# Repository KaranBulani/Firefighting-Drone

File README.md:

# Firefighting-Drone
This project is a drone based approach of fighting fire. It includes functionalities such as generation of area map (using sensors), generation of heat map (using sensors), detection of humans (using sensors) and measuring of toxicity levels using gas sensors. A **grant** from **Mumbai University** was received for this project.
A **research paper** for the same project has been published in **IEEE Xplore**.

To see the working of the project please checkout out the below playlist.

<div align="center">

</div>

Link to the paper **https://ieeexplore.ieee.org/document/9121043**

Link to the paper **https://eudl.eu/doi/10.4108/eai.16-5-2020.2303938**

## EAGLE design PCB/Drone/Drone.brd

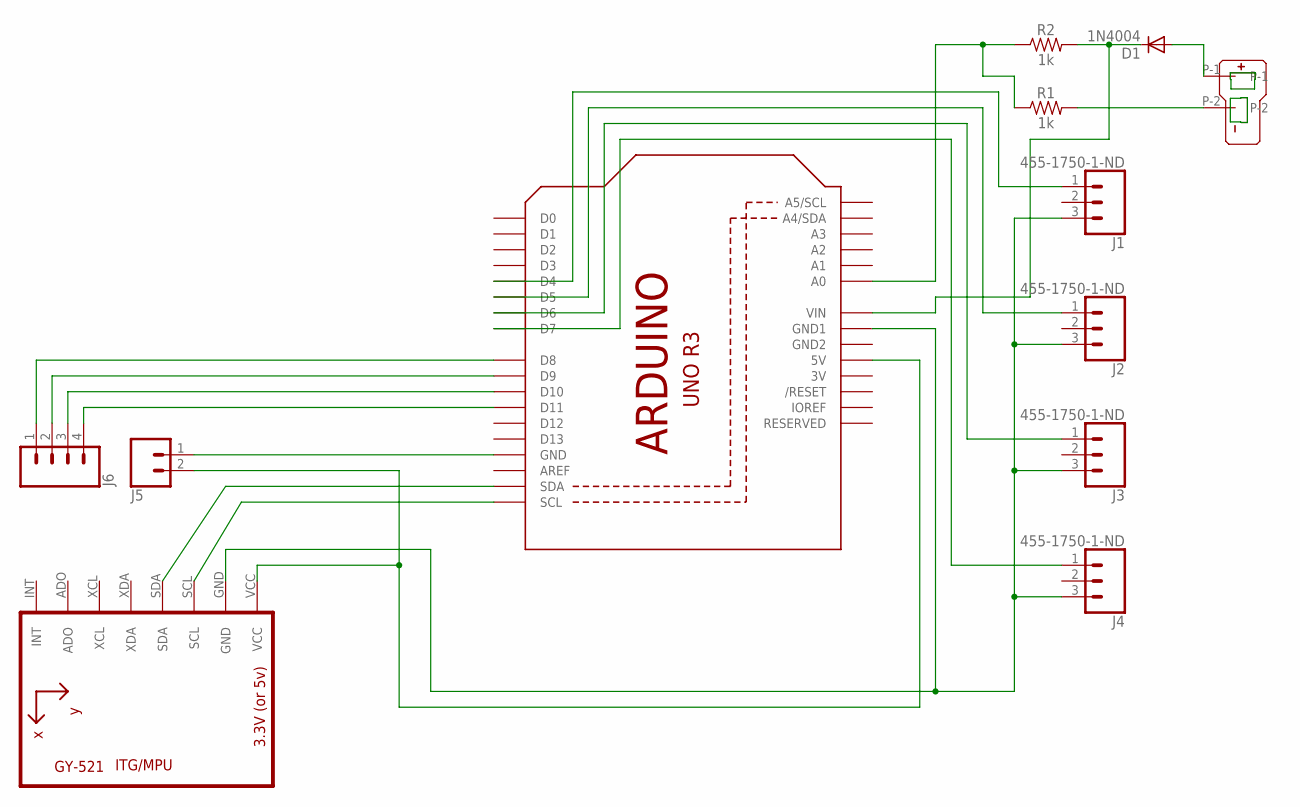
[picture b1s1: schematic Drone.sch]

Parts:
D1: 1N4004; DO41-10
J1, J2, J3, J4: 455-1750-1-ND; 1X03
J5: CONN_02; 1X02
J6: CONN_04JST-PTH; JST-4-PTH
R1, R2: 1k; AXIAL-0.1-KIT
U1: ARDUINOR3-BPLACE
U2: GY-521MPU6050; GY-521
U$1: T-PLUG_CONNECTOR; T_PLUG_CONNECTOR

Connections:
3V: U1.3V
GND2: U1.GND2
unnamed: U1.SCL, U2.SCL
unnamed: U1.SDA, U2.SDA
unnamed: J1.3, J2.3, J3.3, J4.3, U1.GND1, U2.GND
unnamed: J4.1, U1.D7
unnamed: J3.1, U1.D6
unnamed: J2.1, U1.D5
unnamed: J1.1, U1.D4
unnamed: J5.2, U1.5V, U2.VCC
unnamed: J6.1, U1.D8
unnamed: J6.2, U1.D9
unnamed: J6.3, U1.D10
unnamed: J6.4, U1.D11
unnamed: J5.1, U1.GND
unnamed: R1.P$1 (1), R2.P$1 (1), U1.A0
unnamed: R1.P$2 (2), U$1.P-2
unnamed: D1.C, R2.P$2 (2), U1.VIN
unnamed: D1.A, U$1.P-1

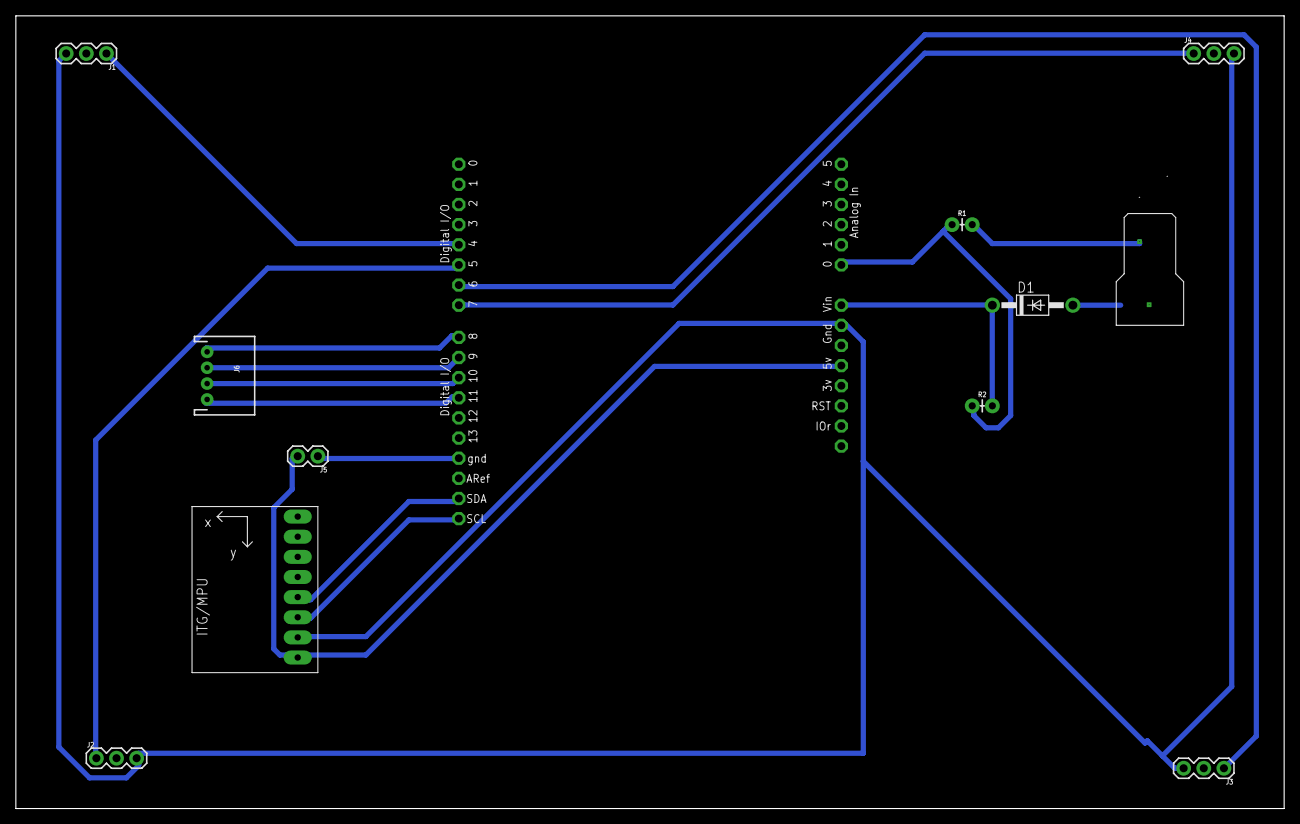
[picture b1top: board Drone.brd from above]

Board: 2 copper layers, 160.0 x 100.0 mm, 12 parts (0 on the bottom side), 17 nets.

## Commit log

2020-02-23 Code for Area Map and Collision Avoidance
2020-08-20 Added code for map generation
2021-04-10 docs: updated readme
2023-09-03 aniket_repo_changes
2023-09-03 aniket repo changes
2023-09-03 aniket repo data
2023-09-03 Panorama making

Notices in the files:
parts and their libraries:
SparkFun-Connectors: Licensing: Creative Commons ShareAlike 4.0 International - https://creativecommons.org/licenses/by-sa/4.0
